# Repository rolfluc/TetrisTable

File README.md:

TetrisTable
===========

This is my attempt at creating the notable game of tetris into a table.

For the board design, I am not an expert nor do I claim to be one, but it is my attempt at creating a re-usable design contains swappable boards in order to allow multi use boards.

The project will be detailed with the standard tetris board, score, and sound. The sound may be driven with a seperate MCU, not sure if the Tetris handling device can handle both a constant stream of music as well as LED/game control.

The hardware components currently being utilized:
WS2812            -       RGB LED
        -       MCU
100W (5V,20A) PSU -       Power Supply
5 Arcade Switches -       Buttons

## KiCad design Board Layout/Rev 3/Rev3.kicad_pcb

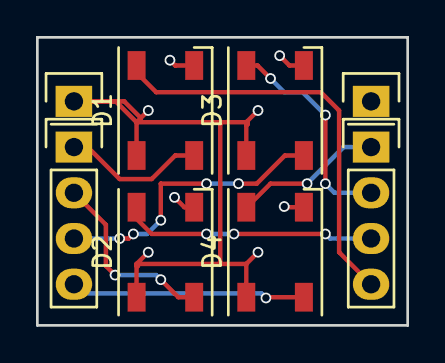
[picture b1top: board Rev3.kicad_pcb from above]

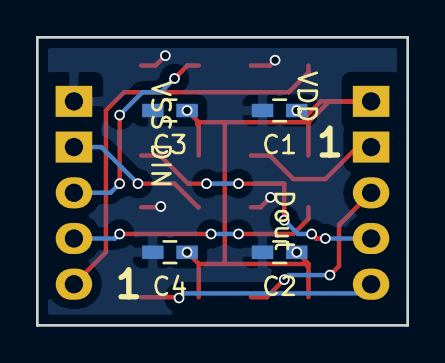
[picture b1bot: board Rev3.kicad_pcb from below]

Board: 2 copper layers, 20.6 x 16.0 mm, 12 parts (4 on the bottom side), 10 nets.

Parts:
C1, C2, C3, C4: C_Small; C_0603_HandSoldering
D1, D2, D3, D4: WS2812B; LED_WS2812B-PLCC4
DIN: DIN; Pin_Header_Straight_1x04
Dout: DOUT; Pin_Header_Straight_1x04
VDD: VDD; Pin_Header_Straight_1x01
VSS: VSS; Pin_Header_Straight_1x01

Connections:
+5V: C1.1, C2.1, C3.1, C4.1, D1.1, D2.1, D3.1, D4.1, VDD.1
GND: C1.2, C2.2, C3.2, C4.2, D1.3, D2.3, D3.3, D4.3, VSS.1
unnamed: D1.2, Dout.1
unnamed: D1.4, DIN.4
unnamed: D2.2, Dout.2
unnamed: D2.4, DIN.3
unnamed: D3.2, Dout.3
unnamed: D3.4, DIN.2
unnamed: D4.2, Dout.4
unnamed: D4.4, DIN.1

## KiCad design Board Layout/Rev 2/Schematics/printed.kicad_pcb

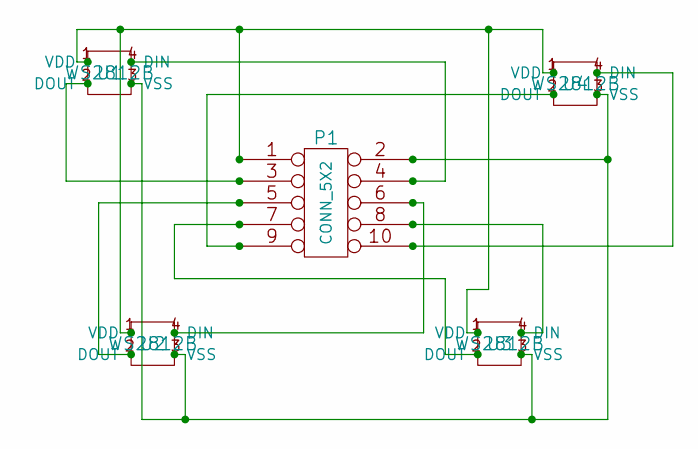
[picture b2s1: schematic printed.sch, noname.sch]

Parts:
P1: CONN_5X2
U1, U2, U3, U4: WS2812B

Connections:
unnamed: P1.7, U3.2 (DOUT)
unnamed: P1.6, U2.4 (DIN)
unnamed: P1.9, U4.2 (DOUT)
unnamed: P1.4, U1.4 (DIN)
unnamed: P1.8, U3.4 (DIN)
unnamed: P1.2, U1.3 (VSS), U2.3 (VSS), U3.3 (VSS), U4.3 (VSS)
unnamed: P1.5, U2.2 (DOUT)
unnamed: P1.10, U4.4 (DIN)
unnamed: P1.3, U1.2 (DOUT)
unnamed: P1.1, U1.1 (VDD), U2.1 (VDD), U3.1 (VDD), U4.1 (VDD)

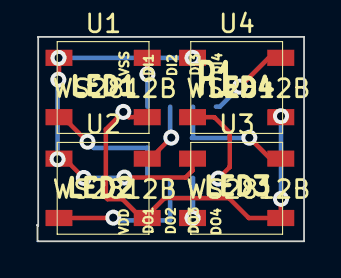
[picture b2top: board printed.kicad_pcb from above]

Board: 2 copper layers, 14.8 x 11.4 mm, 5 parts (0 on the bottom side), 10 nets.

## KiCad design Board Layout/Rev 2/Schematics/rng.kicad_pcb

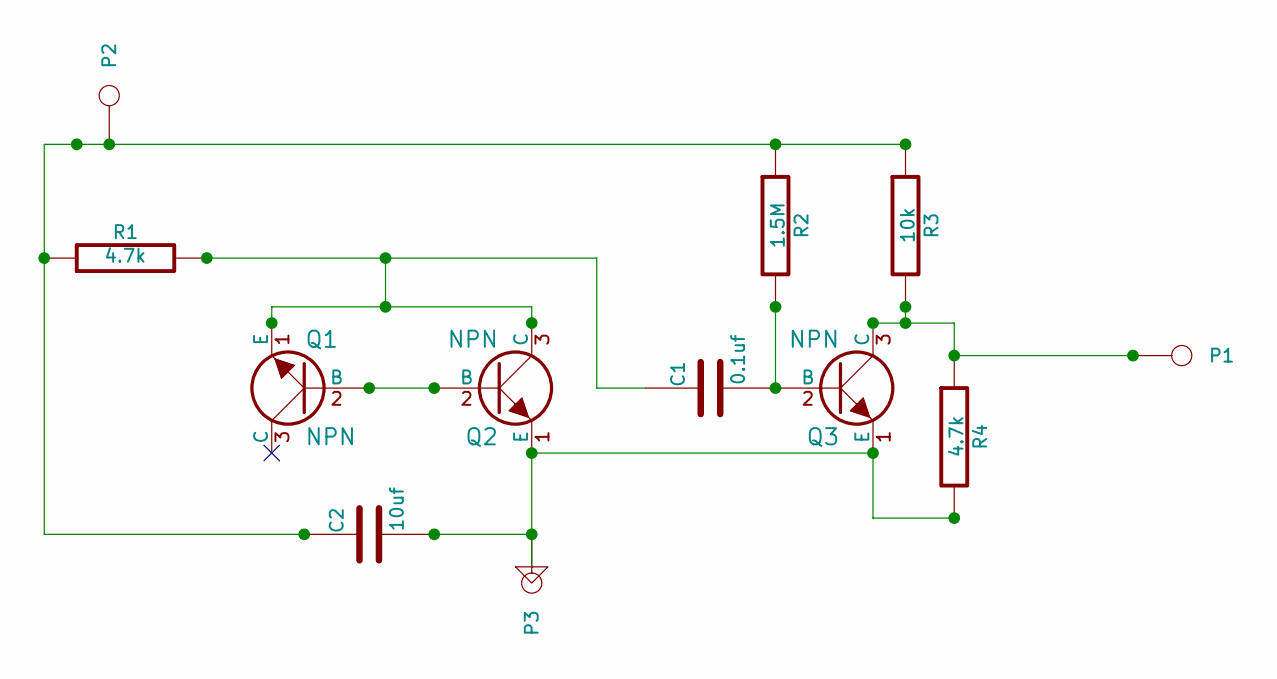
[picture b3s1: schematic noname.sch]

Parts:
C1: 0.1uf
C2: 10uf
P1, P2, P3: CONN_1
Q1, Q2, Q3: NPN
R1, R4: 4.7k
R2: 1.5M
R3: 10k

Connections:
unnamed: C2.2, P3.1, Q2.1 (E), Q3.1 (E), R4.2
unnamed: Q1.2 (B), Q2.2 (B)
unnamed: C1.1, Q1.1 (E), Q2.3 (C), R1.2
unnamed: C1.2, Q3.2 (B), R2.2
unnamed: P1.1, Q3.3 (C), R3.2, R4.1
unnamed: C2.1, P2.1, R1.1, R2.1, R3.1

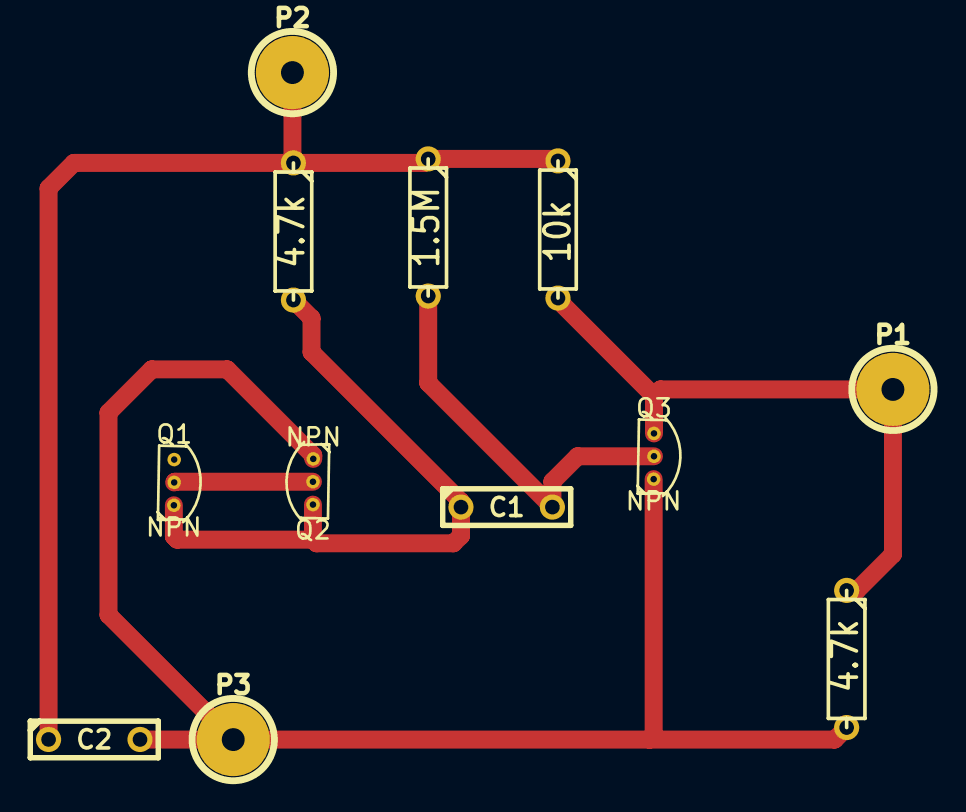
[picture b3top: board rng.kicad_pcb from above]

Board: 2 copper layers, 12 parts (0 on the bottom side), 6 nets.

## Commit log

2014-06-11 Update README.md
    Readme Update
2014-06-13 Ignore all Datasheets
2014-06-25 PCB Files
    Addition of Some Schematic Files
2014-06-26 Approaches
2014-06-26 MPLAB Project addition
2014-06-26 Bit Timing Update
2014-06-28 Bit Timing
    Bit Timing for sending the whole board is done, 400ns spread with a 50us
    end
2014-07-12 Interrupts and new software info
2014-07-13 Interrupt addition
2014-07-17 Colors
    I Think I understand colors.
2014-07-19 Resized Array
    The previous size of the LED array was too large, resizing for
    constraints
2014-07-22 Timer0 Upgrade
    Now operates every 50ms,
2014-08-26 Board Updates
2014-09-03 PCB update
2014-09-04 comments
2014-09-09 Netlist
    Correctly Generated the letlist
2014-09-09 ws2812b schematic file
    missed exporting the file
2014-09-09 Headers Added
2014-09-09 Layout Change
    TODO make even and smaller board
2014-09-10 Final Schematic,
    Nearly to creating the gerber file
2014-09-12 gerber creation
2014-09-12 Project Layout Change
    The layout was changed to better organize
    Also, removed segment about PIC18f4550. It appears as though I may not
    need it any more. Considering PIC32____
2014-11-01 Board 2 start
2014-11-10 Board Update
    not sure if I can do 2 layer as it is too condensed. Might need to
    switch to 4 layer.
2014-11-10 File Export
    WS2812B part needed to be exported and put in correct folder
2014-11-10 Revert "File Export"
    This reverts commit 5946e31f227c92676515fea46d75a5486cffa1b8.
2014-11-10 WS2812b Creation
    Footprint got lost for the WS2812B, rebult it
2014-11-12 Layout Completion
    Verify design is fine via traces and via's; then order. Smaller than v1
2014-11-15 Gerber Creation
    Gerbers of newest type created.
2015-01-21 Random Number Generator
    After some deliberation, a RNG must be used for the tetris pieces.
    generation to be read by the ADC. Takes 12V in to ensure breakdown of
    the B->E threshold. I am not currently satisfied with the trace widths
    or holes for the transistor. To be worked on later.
2015-01-21 Board Completion
    RNG is complete, - Trace widths much larger, condusive to self etching.
2015-01-25 boost converter add
    Added the boost converter. Incomplete.
2015-08-28 Header Change
    Modified the Header to match the 1mm holes standard for 2.54mm.
2015-08-28 Revision 3 Addition
    Added Revision 3, which has a 1206 33pf Capacitor
2015-08-30 Rev 3
    Rev 3 ordered, testing in two weeks.
2015-09-28 Rev 3 - 2
    Added Silk Screen for Pin/LED numbers. Corrected gerbers, sent off the
    zip file to oshpark./
2016-10-03 New Update
    Created a new layout. More condensed. Uses 4 Caps.
2016-11-05 Sent
    Fixed and sent fof an order off 500 of this revision.
